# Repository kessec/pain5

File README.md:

## The Pain 5 Keyboard! 

A 5-key keyboard that depends on pressing keys in combination! Supports up to 120 keys and/or macros!

### Features
- Licensed under [Solderpad Hardware License v2.1](https://solderpad.org/licenses/SHL-2.1/)
- ATMEGA32U4 Based.
- USB-C Support.
- QMK compatible.
- One-handed operation.
- 0603 components (good for hand placing!).
- Comes with all the files for JLCPCB production.

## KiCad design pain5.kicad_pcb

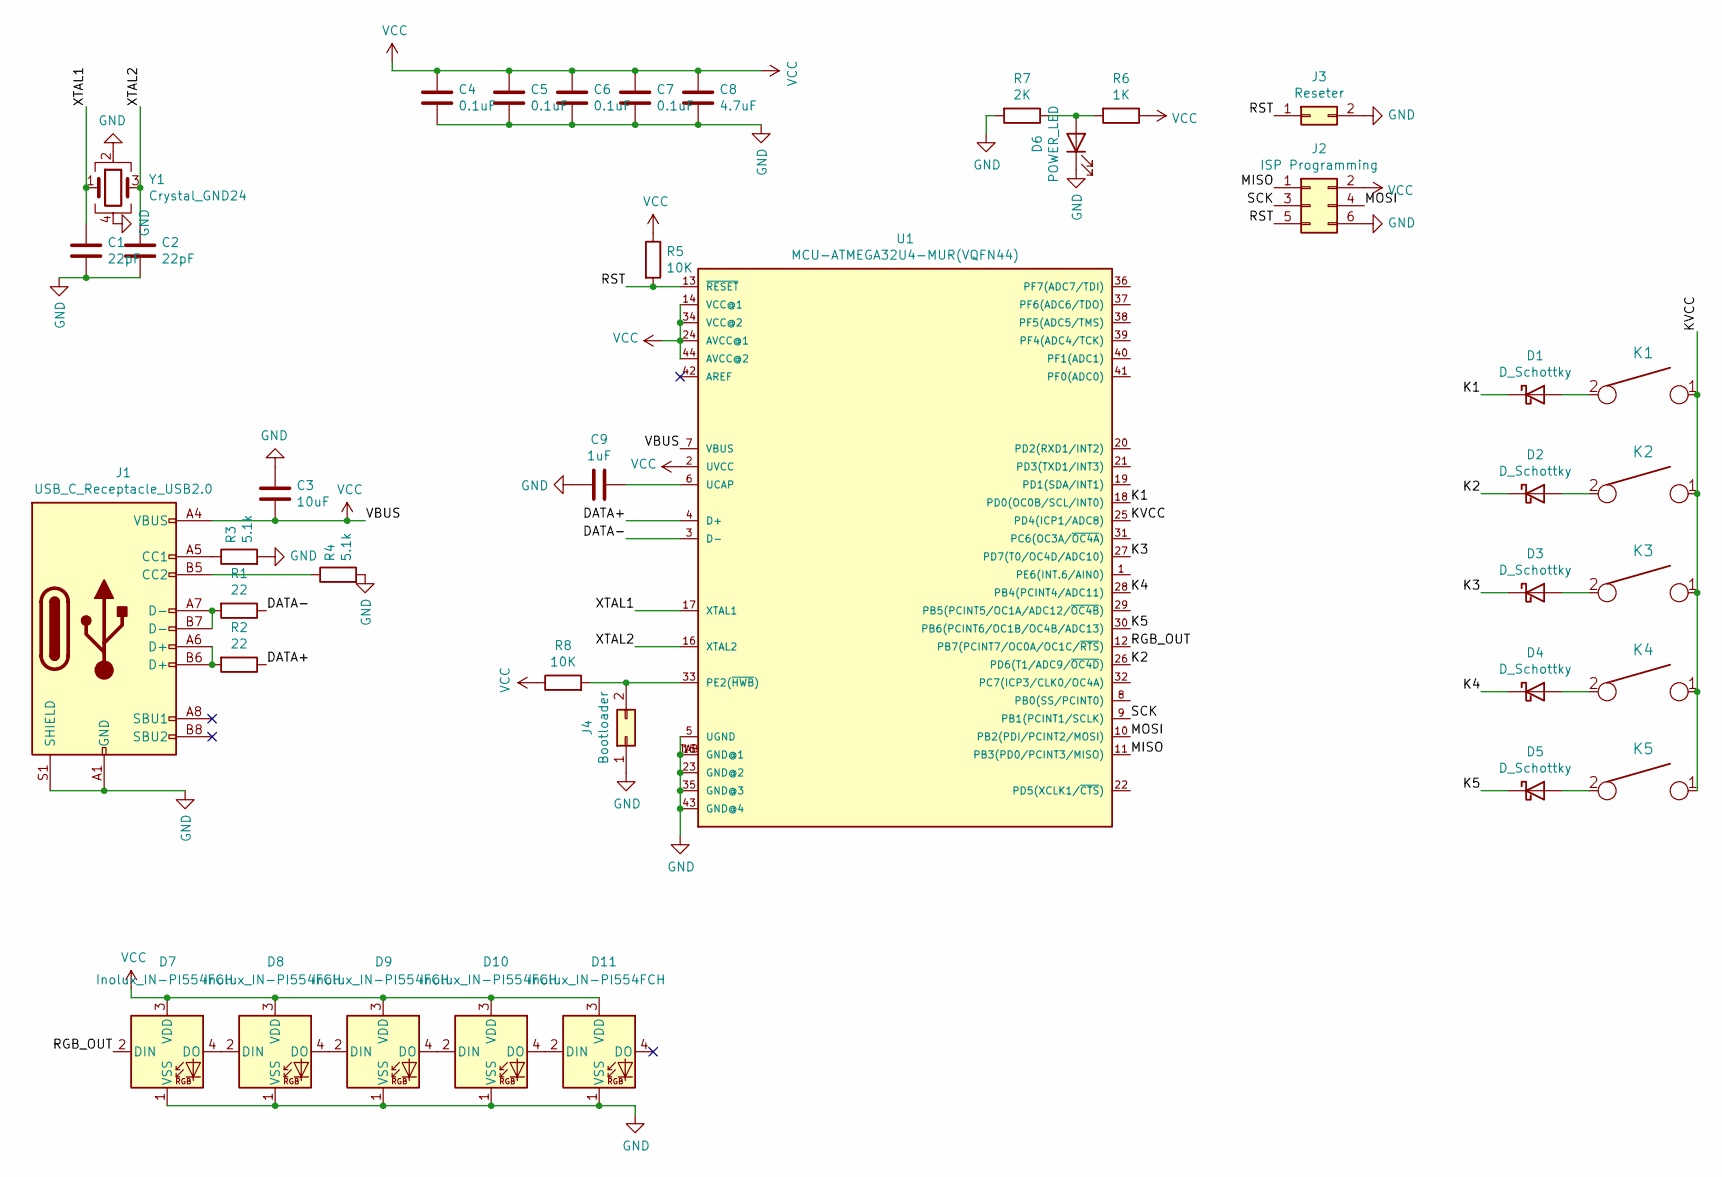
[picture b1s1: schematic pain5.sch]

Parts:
C1, C2: 22pF; C_0603_1608Metric; LCSC C1653
C3: 10uF; C_0603_1608Metric; LCSC C96446
C4, C5, C6, C7: 0.1uF; C_0603_1608Metric; LCSC C170140
C8: 4.7uF; C_0603_1608Metric; LCSC C19666
C9: 1uF; C_0603_1608Metric; LCSC C15849
D1, D2, D3, D4, D5: D_Schottky; D_0603_1608Metric; LCSC C316054
D6: POWER_LED; LED_0603_1608Metric; LCSC C72043
D7, D8, D9, D10, D11: Inolux_IN-PI554FCH; LED_Inolux_IN-PI554FCH_PLCC4_5.0x5.0mm_P3.2mm
J1: USB_C_Receptacle_USB2.0; USB_C_GCT_USB4085
J2: ISP Programming; PinHeader_1x06_P1.00mm_Vertical
J3: Reseter; PinHeader_1x02_P1.00mm_Vertical
J4: Bootloader; PinHeader_1x02_P1.00mm_Vertical
K1, K2, K3, K4, K5: KEYSW; SW_Cherry_MX_PCB_1.00u
R1, R2: 22; R_0603_1608Metric; LCSC C23345
R3, R4: 5.1k; R_0603_1608Metric; LCSC C23186
R5, R8: 10K; R_0603_1608Metric; LCSC C25804
R6: 1K; R_0603_1608Metric; LCSC C21190
R7: 2K; R_0603_1608Metric; LCSC C22975
U1: MCU-ATMEGA32U4-MUR(VQFN44); QFP80P1200X1200X120-44N; MPN ATMEGA32U4-MUR; LCSC C45874
Y1: Crystal_GND24; Crystal_SMD_3225-4Pin_3.2x2.5mm; LCSC C13738

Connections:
/DATA+: R2.1, U1.4 (D+)
/DATA-: R1.1, U1.3 (D-)
/K1: D1.1 (K), U1.18 (PD0(OC0B/SCL/INT0))
/K2: D2.1 (K), U1.26 (PD6(T1/ADC9/~OC4D))
/K3: D3.1 (K), U1.27 (PD7(T0/OC4D/ADC10))
/K4: D4.1 (K), U1.28 (PB4(PCINT4/ADC11))
/K5: D5.1 (K), U1.30 (PB6(PCINT6/OC1B/OC4B/ADC13))
/KVCC: K1.1, K2.1, K3.1, K4.1, K5.1, U1.25 (PD4(ICP1/ADC8))
/MISO: J2.1, U1.11 (PB3(PD0/PCINT3/MISO))
/MOSI: J2.4, U1.10 (PB2(PDI/PCINT2/MOSI))
/RGB_OUT: D7.2 (DIN), U1.12 (PB7(PCINT7/OC0A/OC1C/~RTS))
/RST: J2.5, J3.1, R5.2, U1.13 (~RESET)
/SCK: J2.3, U1.9 (PB1(PCINT1/SCLK))
/XTAL1: C1.1, U1.17 (XTAL1), Y1.1
/XTAL2: C2.1, U1.16 (XTAL2), Y1.3
GND: C1.2, C2.2, C3.2, C4.2, C5.2, C6.2, C7.2, C8.2, C9.2, D6.1 (K), D7.1 (VSS), D8.1 (VSS), D9.1 (VSS), D10.1 (VSS), D11.1 (VSS), J1.A1 (GND), J1.A12 (GND), J1.B1 (GND), J1.B12 (GND), J1.S1 (SHIELD), J2.6, J3.2, J4.1, R3.2, R4.2, R7.2, U1.5 (UGND), U1.15 (GND@1), U1.23 (GND@2), U1.35 (GND@3), U1.43 (GND@4), U1.TAB (GND@1), Y1.2, Y1.4
unnamed: C9.1, U1.6 (UCAP)
unnamed: D1.2 (A), K1.2
unnamed: D2.2 (A), K2.2
unnamed: D3.2 (A), K3.2
unnamed: D4.2 (A), K4.2
unnamed: D5.2 (A), K5.2
unnamed: D6.2 (A), R6.2, R7.1
unnamed: D7.4 (DO), D8.2 (DIN)
unnamed: D8.4 (DO), D9.2 (DIN)
unnamed: D9.4 (DO), D10.2 (DIN)
unnamed: D10.4 (DO), D11.2 (DIN)
unnamed: J1.A5 (CC1), R3.1
unnamed: J1.A6 (D+), J1.B6 (D+), R2.2
unnamed: J1.A7 (D-), J1.B7 (D-), R1.2
unnamed: J1.B5 (CC2), R4.1
unnamed: J4.2, R8.2, U1.33 (PE2(~HWB))
VCC: C3.1, C4.1, C5.1, C6.1, C7.1, C8.1, D7.3 (VDD), D8.3 (VDD), D9.3 (VDD), D10.3 (VDD), D11.3 (VDD), J1.A4 (VBUS), J1.A9 (VBUS), J1.B4 (VBUS), J1.B9 (VBUS), J2.2, R5.1, R6.1, R8.1, U1.2 (UVCC), U1.7 (VBUS), U1.14 (VCC@1), U1.24 (AVCC@1), U1.34 (VCC@2), U1.44 (AVCC@2)

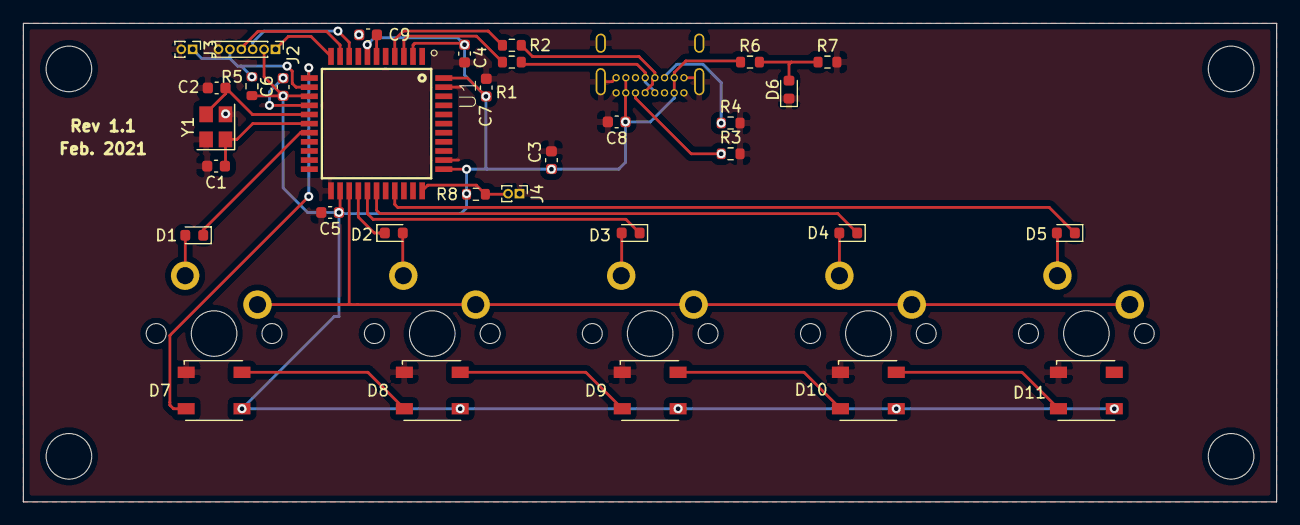
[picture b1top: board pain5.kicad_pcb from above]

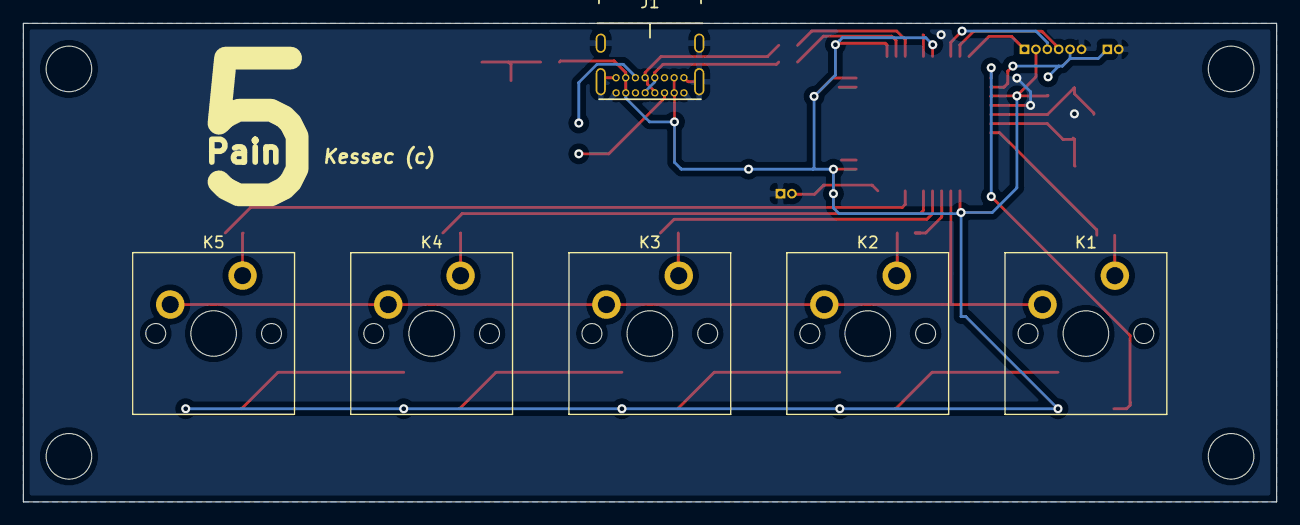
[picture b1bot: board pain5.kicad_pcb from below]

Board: 2 copper layers, 110.0 x 42.0 mm, 39 parts (6 on the bottom side), 33 nets.

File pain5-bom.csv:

"Id";"Designator";"Package";"Quantity";"Designation";"Supplier and ref";
1;"kessec-logo1";"kessec-logo1";1;"";;;
2;"REF**";"ESD-Logo_6.6x6mm_SilkScreen";1;"ESD-Logo_6.6x6mm_SilkScreen";;;
3;"REF**";"OSHW-Logo2_9.8x8mm_SilkScreen";1;"OSHW-Logo2_9.8x8mm_SilkScreen";;;
4;"K5,K5,K2,K3,K4";"SW_Cherry_MX_PCB_1.00u";5;"KEYSW";;;
5;"C1,C2";"C_0603_1608Metric";2;"22pF";;;
6;"C3";"C_0603_1608Metric";1;"10uF";;;
7;"C4,C5,C6,C7";"C_0603_1608Metric";4;"0.1uF";;;
8;"C8";"C_0603_1608Metric";1;"4.7uF";;;
9;"C9";"C_0603_1608Metric";1;"1uF";;;
10;"D1,D2,D3,D4,D5";"D_0603_1608Metric";5;"D_Schottky";;;
11;"J1";"USB_C_GCT_USB4085";1;"USB_C_Receptacle_USB2.0";;;
12;"J2";"PinHeader_2x03_P1.00mm_Vertical";1;"ISP Programming";;;
13;"J3";"PinHeader_1x02_P1.00mm_Vertical";1;"Reseter";;;
14;"R1,R2";"R_0603_1608Metric";2;"22";;;
15;"R3,R4";"R_0603_1608Metric";2;"5.1k";;;
16;"U1";"QFN44G-0.5-7X7MM";1;"MCU-ATMEGA32U4-MUR(VQFN44)";;;
17;"Y1";"Crystal_SMD_3225-4Pin_3.2x2.5mm";1;"Crystal_GND24";;;

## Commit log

2020-12-16 [upload] all the files im currently using
2020-12-16 [upload] fixes
2020-12-21 [upload] pretty
2020-12-21 Create LICENSE
2020-12-22 [tweak] i don't wanna write it all
2021-01-17 [upload] added a lot more
2021-01-17 [tweak] right sizing
2021-02-14 [tweak] rgb update :)
2021-02-15 [update] updated pictues and sym lib
